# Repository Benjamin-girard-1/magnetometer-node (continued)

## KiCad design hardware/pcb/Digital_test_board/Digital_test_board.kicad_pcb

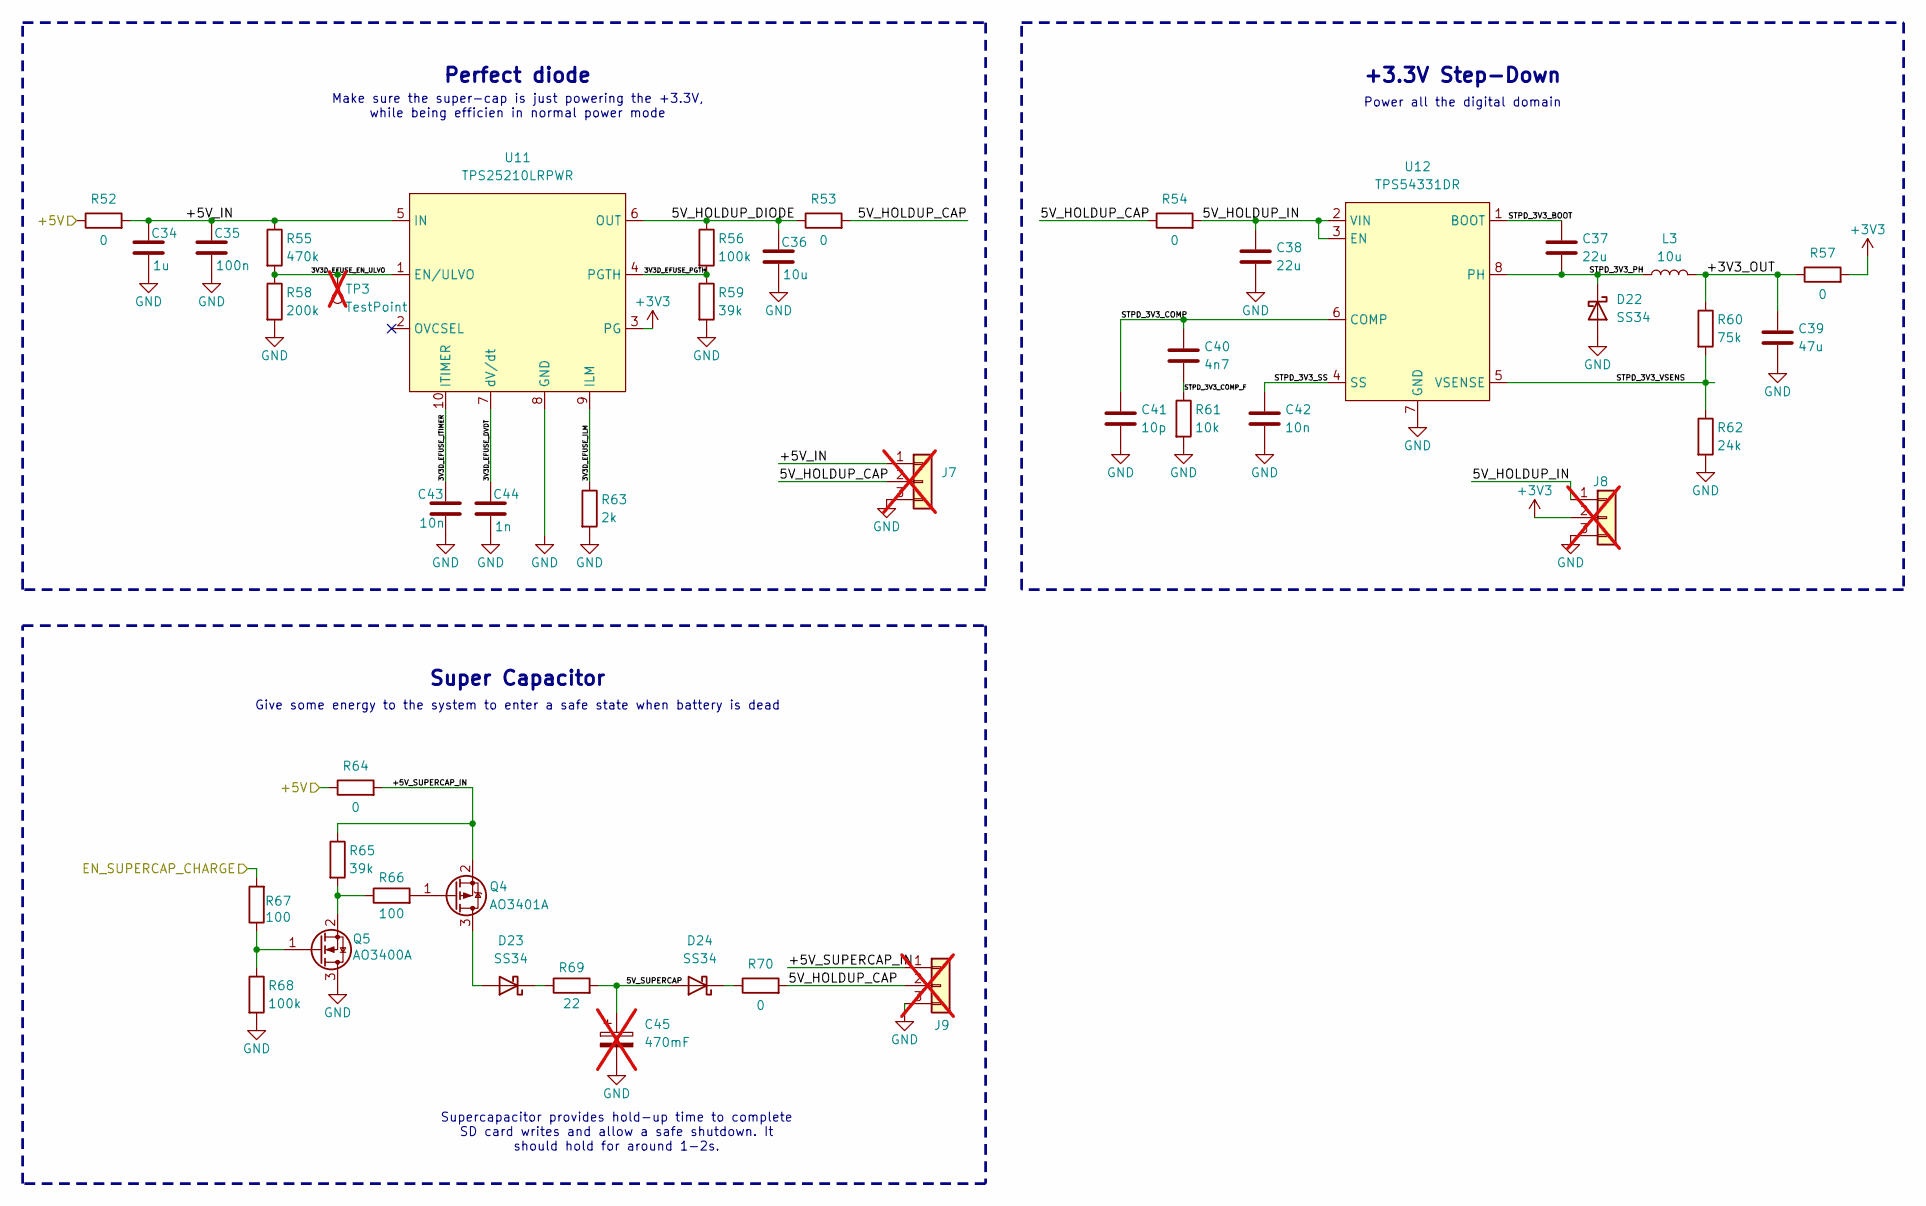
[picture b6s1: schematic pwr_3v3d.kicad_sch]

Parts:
C34: 1u; C_0805_2012Metric; LCSC C28323
C35: 100n; C_0603_1608Metric; LCSC C14663
C36: 10u; C_0805_2012Metric; LCSC C15850
C37, C38: 22u; C_1206_3216Metric; LCSC C12891
C39: 47u; C_1206_3216Metric; LCSC C96123
C40: 4n7; C_0603_1608Metric; LCSC C53987
C41: 10p; C_0603_1608Metric; LCSC C1634
C42, C43: 10n; C_0603_1608Metric; LCSC C57112
C44: 1n; C_0603_1608Metric; LCSC C1588
C45: 470mF; C_Radial_D8.0mm_P11.50mm; not fitted
D22, D23, D24: SS34; D_SMA; LCSC C8678
J7, J8, J9: Conn_01x03; PinHeader_1x03_P2.54mm_Vertical; not fitted
L3: 10u; L_Sunlord_MWSA0503S; LCSC C177248
Q4: AO3401A; SOT-23; LCSC C15127
Q5: AO3400A; SOT-23; LCSC C20917
R52, R53, R54, R57, R64, R70: 0; R_1206_3216Metric; LCSC C17888
R55: 470k; R_0603_1608Metric; LCSC C23178
R56, R68: 100k; R_0603_1608Metric; LCSC C25803
R58: 200k; R_0603_1608Metric; LCSC C25811
R59, R65: 39k; R_0603_1608Metric; LCSC C23153
R60: 75k; R_0603_1608Metric; LCSC C23242
R61: 10k; R_0603_1608Metric; LCSC C25804
R62: 24k; R_0603_1608Metric; LCSC C23352
R63: 2k; R_0603_1608Metric; LCSC C22975
R66, R67: 100; R_0603_1608Metric; LCSC C22775
R69: 22; R_2512_6332Metric; LCSC C2974113
TP3: TestPoint; TestPoint_THTPad_1.0x1.0mm_Drill0.5mm; not fitted
U11: TPS25210LRPWR; VQFN-HR-10; LCSC C2861226
U12: TPS54331DR; SOIC-8_3.9x4.9mm_P1.27mm; LCSC C9865

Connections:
+3V3: J8.2, R57.2, U11.3 (PG); also elsewhere on the board
+5V: R52.1, R64.1; also elsewhere on the board
/PWR_3V3D/3V3D_EFUSE_DVDT: C44.1, U11.7 (dV/dt)
/PWR_3V3D/3V3D_EFUSE_EN_ULVO: R55.2, R58.1, TP3.1, U11.1 (EN/ULVO)
/PWR_3V3D/3V3D_EFUSE_ILM: R63.1, U11.9 (ILM)
/PWR_3V3D/3V3D_EFUSE_ITIMER: C43.1, U11.10 (ITIMER)
/PWR_3V3D/3V3D_EFUSE_PGTH: R56.2, R59.1, U11.4 (PGTH)
/PWR_3V3D/5V_CAP_CHG: D23.1 (K), R69.1
/PWR_3V3D/5V_HOLDUP: C36.1, R53.1, R56.1, U11.6 (OUT)
/PWR_3V3D/5V_HOLDUP_IN: C38.1, J8.1, R54.2, U12.2 (VIN), U12.3 (EN)
/PWR_3V3D/5V_HOLDUP_bridge: J7.2, J9.2, R53.2, R54.1, R70.2
/PWR_3V3D/5V_SUPERCAP: C45.1, D24.2 (A), R69.2
/PWR_3V3D/5V_SUPERCAP_OUT: D24.1 (K), R70.1
/PWR_3V3D/+3V3_OUT: C39.1, L3.2, R57.1, R60.1
/PWR_3V3D/+5V_CAP_CHG_SW: D23.2 (A), Q4.3 (D)
/PWR_3V3D/+5V_IN: C34.1, C35.1, J7.1, R52.2, R55.1, U11.5 (IN)
/PWR_3V3D/+5V_SUPERCAP_IN: J9.1, Q4.2 (S), R64.2, R65.1
/PWR_3V3D/STPD_3V3_BOOT: C37.1, U12.1 (BOOT)
/PWR_3V3D/STPD_3V3_COMP: C40.1, C41.1, U12.6 (COMP)
/PWR_3V3D/STPD_3V3_COMP_F: C40.2, R61.1
/PWR_3V3D/STPD_3V3_PH: C37.2, D22.1 (K), L3.1, U12.8 (PH)
/PWR_3V3D/STPD_3V3_SS: C42.1, U12.4 (SS)
/PWR_3V3D/STPD_3V3_VSENS: R60.2, R62.1, U12.5 (VSENSE)
/PWR_3V3D/SUPERCAP_CHG_GATE: Q4.1 (G), R66.2
/PWR_3V3D/SUPERCAP_CHG_GATE_PULL: Q5.2 (S), R65.2, R66.1
GND: C34.2, C35.2, C36.2, C38.2, C39.2, C41.2, C42.2, C43.2, C44.2, C45.2, D22.2 (A), J7.3, J8.3, J9.3, Q5.3 (D), R58.2, R59.2, R61.2, R62.2, R63.2, R68.2, U11.8 (GND), U12.7 (GND); also elsewhere on the board

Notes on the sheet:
Make sure the super-cap is just powering the +3.3V, while being efficien in normal power mode
Super Capacitor
Give some energy to the system to enter a safe state when battery is dead
+3.3V Step-Down
Power all the digital domain
Supercapacitor provides hold-up time to complete SD card writes and allow a safe shutdown. It should hold for around 1-2s.
Perfect diode

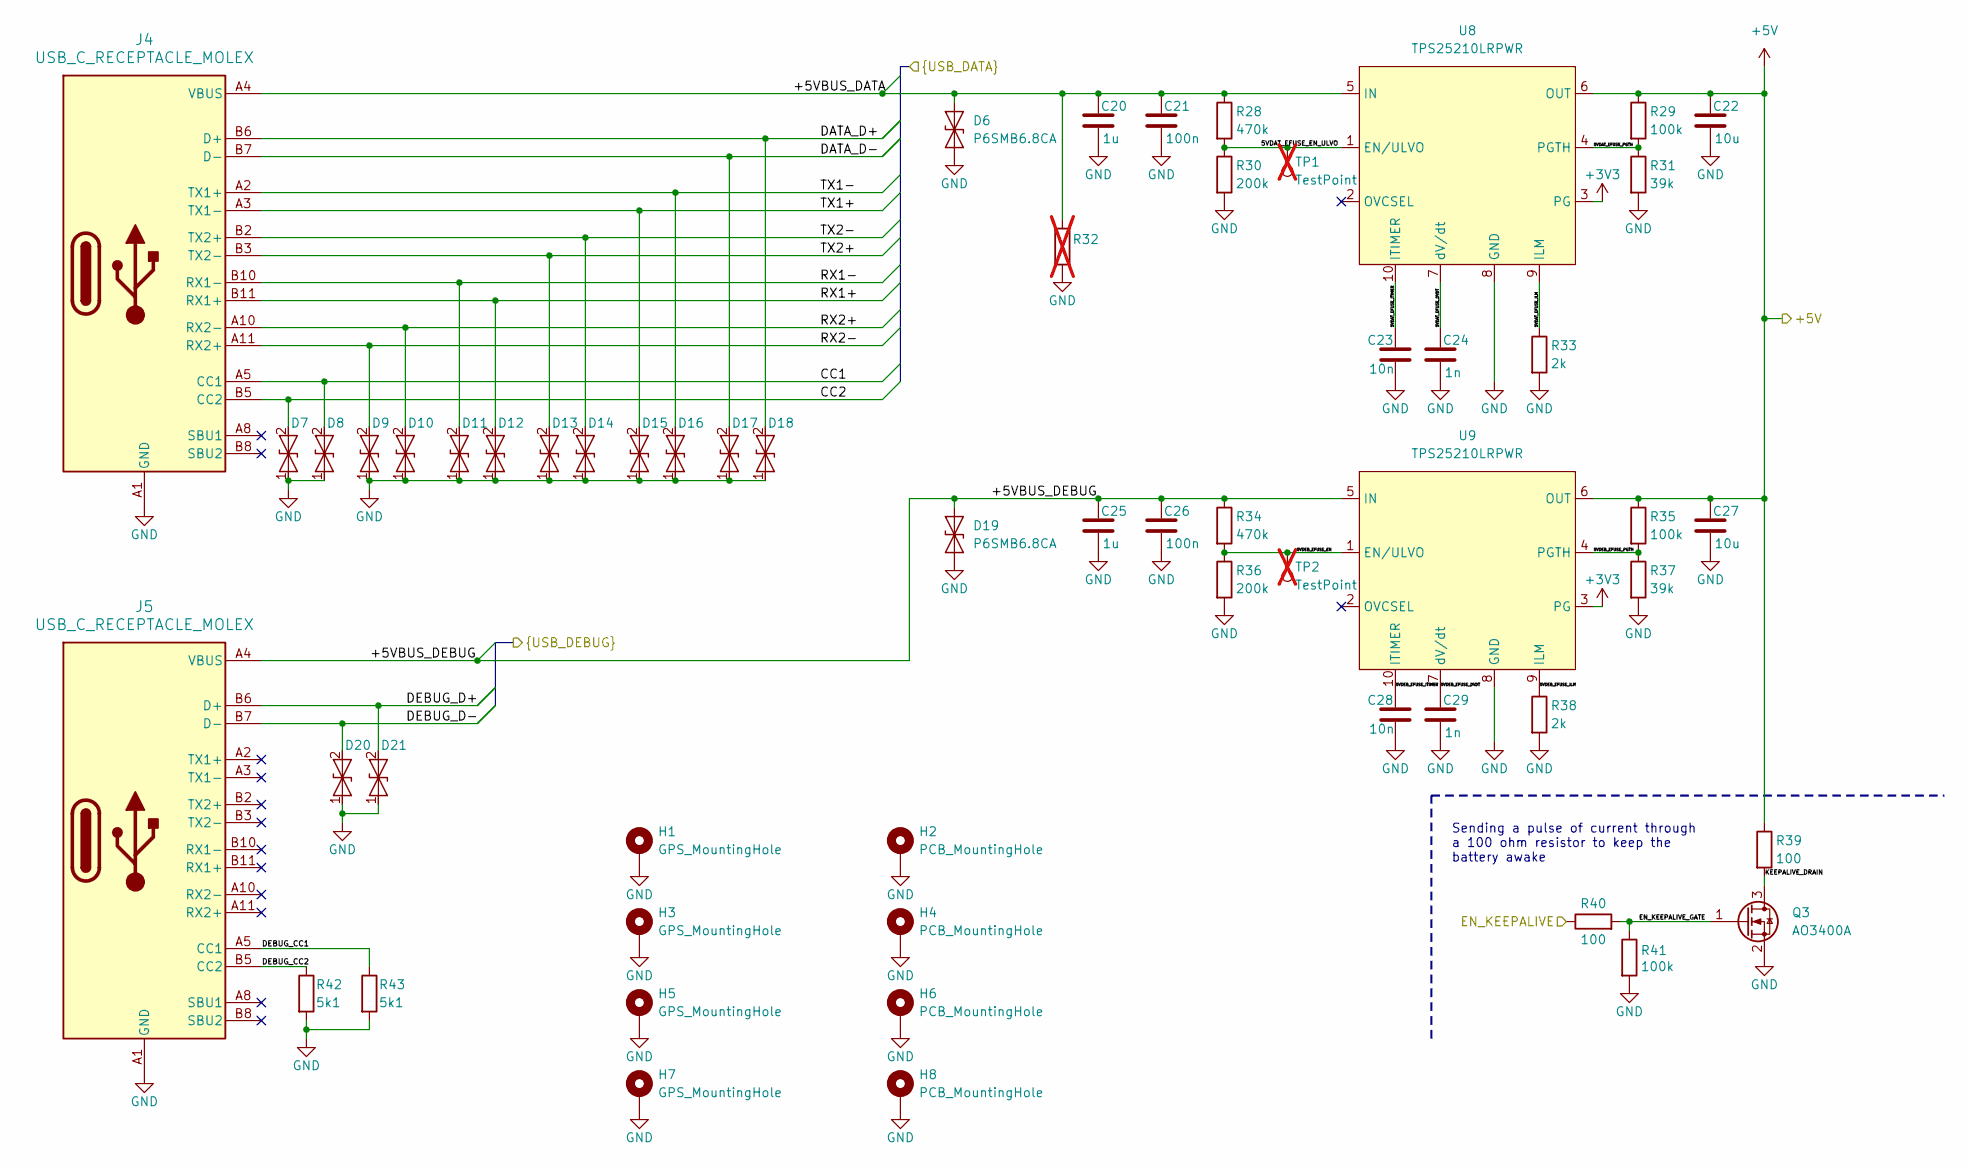
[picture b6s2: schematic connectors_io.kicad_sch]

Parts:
C20, C25: 1u; C_0805_2012Metric; LCSC C28323
C21, C26: 100n; C_0603_1608Metric; LCSC C14663
C22, C27: 10u; C_0805_2012Metric; LCSC C15850
C23, C28: 10n; C_0603_1608Metric; LCSC C57112
C24, C29: 1n; C_0603_1608Metric; LCSC C1588
D6, D19: P6SMB6.8CA; D_SMB; LCSC C7420377
D7, D8, D9, D10, D11, D12, D13, D14, D15, D16, D17, D18, D20, D21: H5VUD5BB; D_SOD-523; LCSC C20615820
H1, H3, H5, H7: GPS_MountingHole; MountingHole_3.2mm_M3_DIN965_Pad_TopBottom
H2, H4, H6, H8: PCB_MountingHole; MountingHole_3.2mm_M3_DIN965_Pad_TopBottom
J4, J5: USB_C_RECEPTACLE_MOLEX; CONN_201267-0005_MOL; LCSC C565324
Q3: AO3400A; SOT-23; LCSC C20917
R28, R34: 470k; R_0603_1608Metric; LCSC C23178
R29, R35, R41: 100k; R_0603_1608Metric; LCSC C25803
R30, R36: 200k; R_0603_1608Metric; LCSC C25811
R31, R37: 39k; R_0603_1608Metric; LCSC C23153
R32: R_1206_3216Metric_Pad1.30x1.75mm_HandSolder; not fitted
R33, R38: 2k; R_0603_1608Metric; LCSC C22975
R39, R40: 100; R_0603_1608Metric; LCSC C22775
R42, R43: 5k1; R_0603_1608Metric; LCSC C23186
TP1, TP2: TestPoint; TestPoint_THTPad_1.0x1.0mm_Drill0.5mm; not fitted
U8, U9: TPS25210LRPWR; VQFN-HR-10; LCSC C2861226

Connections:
+3V3: U8.3 (PG), U9.3 (PG); also elsewhere on the board
+5V: C22.1, C27.1, R29.1, R35.1, R39.1, U8.6 (OUT), U9.6 (OUT); also elsewhere on the board
/DATA_SAVING/+5VBUS_DATA: C20.1, C21.1, D6.2 (A2), J4.A4 (VBUS), J4.A9 (VBUS), J4.B4 (VBUS), J4.B9 (VBUS), R28.1, R32.2, U8.5 (IN); also elsewhere on the board
/DATA_SAVING/CC1: D8.2, J4.A5 (CC1); also elsewhere on the board
/DATA_SAVING/CC2: D7.2, J4.B5 (CC2); also elsewhere on the board
/DATA_SAVING/DATA_D+: D18.2, J4.A6 (D+), J4.B6 (D+); also elsewhere on the board
/DATA_SAVING/DATA_D-: D17.2, J4.A7 (D-), J4.B7 (D-); also elsewhere on the board
/DATA_SAVING/RX1+: D12.2, J4.B11 (RX1+); also elsewhere on the board
/DATA_SAVING/RX1-: D11.2, J4.B10 (RX1-); also elsewhere on the board
/DATA_SAVING/RX2+: D10.2, J4.A10 (RX2-); also elsewhere on the board
/DATA_SAVING/RX2-: D9.2, J4.A11 (RX2+); also elsewhere on the board
/DATA_SAVING/TX1+: D15.2, J4.A3 (TX1-); also elsewhere on the board
/DATA_SAVING/TX1-: D16.2, J4.A2 (TX1+); also elsewhere on the board
/DATA_SAVING/TX2+: D13.2, J4.B3 (TX2-); also elsewhere on the board
/DATA_SAVING/TX2-: D14.2, J4.B2 (TX2+); also elsewhere on the board
/IO_CONNECTOR/5VDAT_EFUSE_DVDT: C24.1, U8.7 (dV/dt)
/IO_CONNECTOR/5VDAT_EFUSE_EN_ULVO: R28.2, R30.1, TP1.1, U8.1 (EN/ULVO)
/IO_CONNECTOR/5VDAT_EFUSE_ILM: R33.1, U8.9 (ILM)
/IO_CONNECTOR/5VDAT_EFUSE_ITIMER: C23.1, U8.10 (ITIMER)
/IO_CONNECTOR/5VDAT_EFUSE_PGTH: R29.2, R31.1, U8.4 (PGTH)
/IO_CONNECTOR/5VDEB_EFUSE_DVDT: C29.1, U9.7 (dV/dt)
/IO_CONNECTOR/5VDEB_EFUSE_EN: R34.2, R36.1, TP2.1, U9.1 (EN/ULVO)
/IO_CONNECTOR/5VDEB_EFUSE_ILM: R38.1, U9.9 (ILM)
/IO_CONNECTOR/5VDEB_EFUSE_ITIMER: C28.1, U9.10 (ITIMER)
/IO_CONNECTOR/5VDEB_EFUSE_PGTH: R35.2, R37.1, U9.4 (PGTH)
/IO_CONNECTOR/+5VBUS_DEBUG: C25.1, C26.1, D19.2 (A2), J5.A4 (VBUS), J5.A9 (VBUS), J5.B4 (VBUS), J5.B9 (VBUS), R34.1, U9.5 (IN); also elsewhere on the board
/IO_CONNECTOR/DEBUG_CC1: J5.A5 (CC1), R43.1
/IO_CONNECTOR/DEBUG_CC2: J5.B5 (CC2), R42.1
/IO_CONNECTOR/DEBUG_D+: D21.2, J5.A6 (D+), J5.B6 (D+); also elsewhere on the board
/IO_CONNECTOR/DEBUG_D-: D20.2, J5.A7 (D-), J5.B7 (D-); also elsewhere on the board
/IO_CONNECTOR/EN_KEEPALIVE: R40.1; also elsewhere on the board
/IO_CONNECTOR/EN_KEEPALIVE_GATE: Q3.1 (G), R40.2, R41.1
/IO_CONNECTOR/KEEPALIVE_DRAIN: Q3.3 (D), R39.2
GND: C20.2, C21.2, C22.2, C23.2, C24.2, C25.2, C26.2, C27.2, C28.2, C29.2, D6.1 (A1), D7.1, D8.1, D9.1, D10.1, D11.1, D12.1, D13.1, D14.1, D15.1, D16.1, D17.1, D18.1, D19.1 (A1), D20.1, D21.1, H1.1, H2.1, H3.1, H4.1, H5.1, H6.1, H7.1, H8.1, J4.A1 (GND), J4.A12 (GND), J4.B1 (GND), J4.B12 (GND), J5.A1 (GND), J5.A12 (GND), J5.B1 (GND), J5.B12 (GND), Q3.2 (S), R30.2, R31.2, R32.1, R33.2, R36.2, R37.2, R38.2, R41.2, R42.2, R43.2, U8.8 (GND), U9.8 (GND); also elsewhere on the board

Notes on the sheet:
Sending a pulse of current through a 100 ohm resistor to keep the battery awake

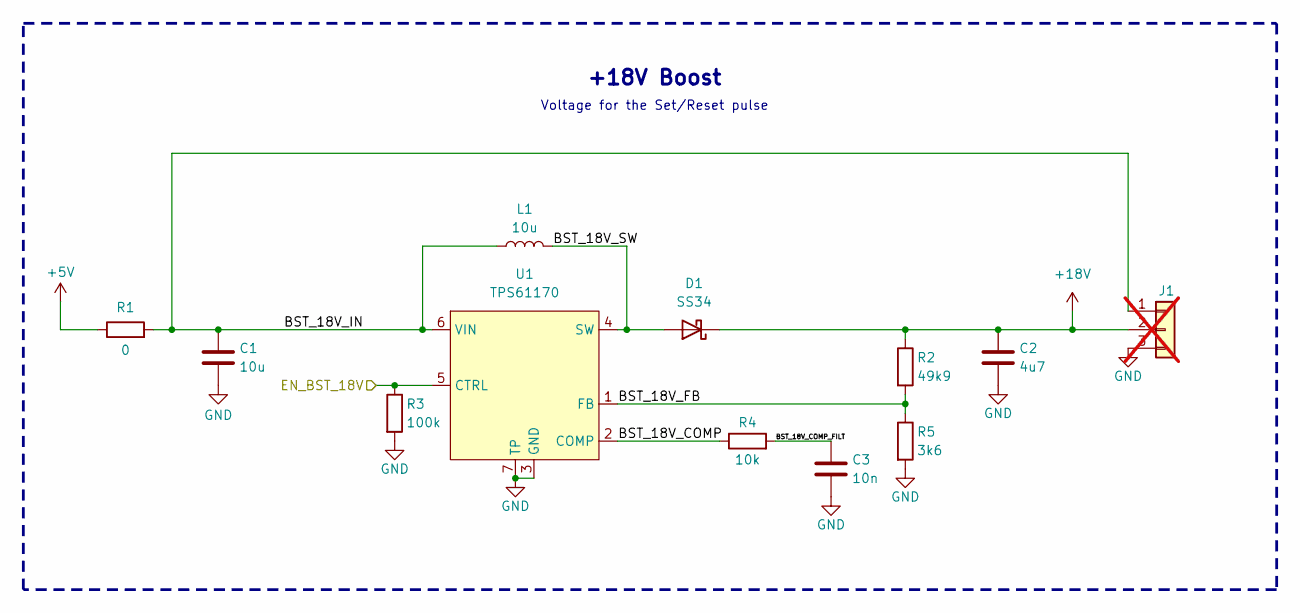
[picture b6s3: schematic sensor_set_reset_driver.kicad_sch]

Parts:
C1: 10u; C_0805_2012Metric; LCSC C15850
C2: 4u7; C_1206_3216Metric; LCSC C29823
C3: 10n; C_0603_1608Metric; LCSC C57112
D1: SS34; D_SMA; LCSC C8678
J1: Conn_01x03; PinHeader_1x03_P2.54mm_Vertical; not fitted
L1: 10u; L_Sunlord_MWSA0503S; LCSC C177248
R1: 0; R_1206_3216Metric; LCSC C17888
R2: 49k9; R_0603_1608Metric; LCSC C23184
R3: 100k; R_0603_1608Metric; LCSC C25803
R4: 10k; R_0603_1608Metric; LCSC C25804
R5: 3k6; R_0603_1608Metric; LCSC C22980
U1: TPS61170; WSON-6-1EP_2x2mm_P0.65mm_EP1x1.6mm; LCSC C15163

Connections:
+5V: R1.1; also elsewhere on the board
+18V: C2.1, D1.1 (K), J1.2, R2.1
/MCU_ESP32S3/EN_BST_18V: R3.1, U1.5 (CTRL); also elsewhere on the board
/SENSOR_SET_RESET_DRIVER/BST_18V_COMP: R4.1, U1.2 (COMP)
/SENSOR_SET_RESET_DRIVER/BST_18V_COMP_FILT: C3.1, R4.2
/SENSOR_SET_RESET_DRIVER/BST_18V_FB: R2.2, R5.1, U1.1 (FB)
/SENSOR_SET_RESET_DRIVER/BST_18V_IN: C1.1, J1.1, L1.1, R1.2, U1.6 (VIN)
/SENSOR_SET_RESET_DRIVER/BST_18V_SW: D1.2 (A), L1.2, U1.4 (SW)
GND: C1.2, C2.2, C3.2, J1.3, R3.2, R5.2, U1.3 (GND), U1.7 (TP); also elsewhere on the board

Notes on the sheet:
+18V Boost
Voltage for the Set/Reset pulse

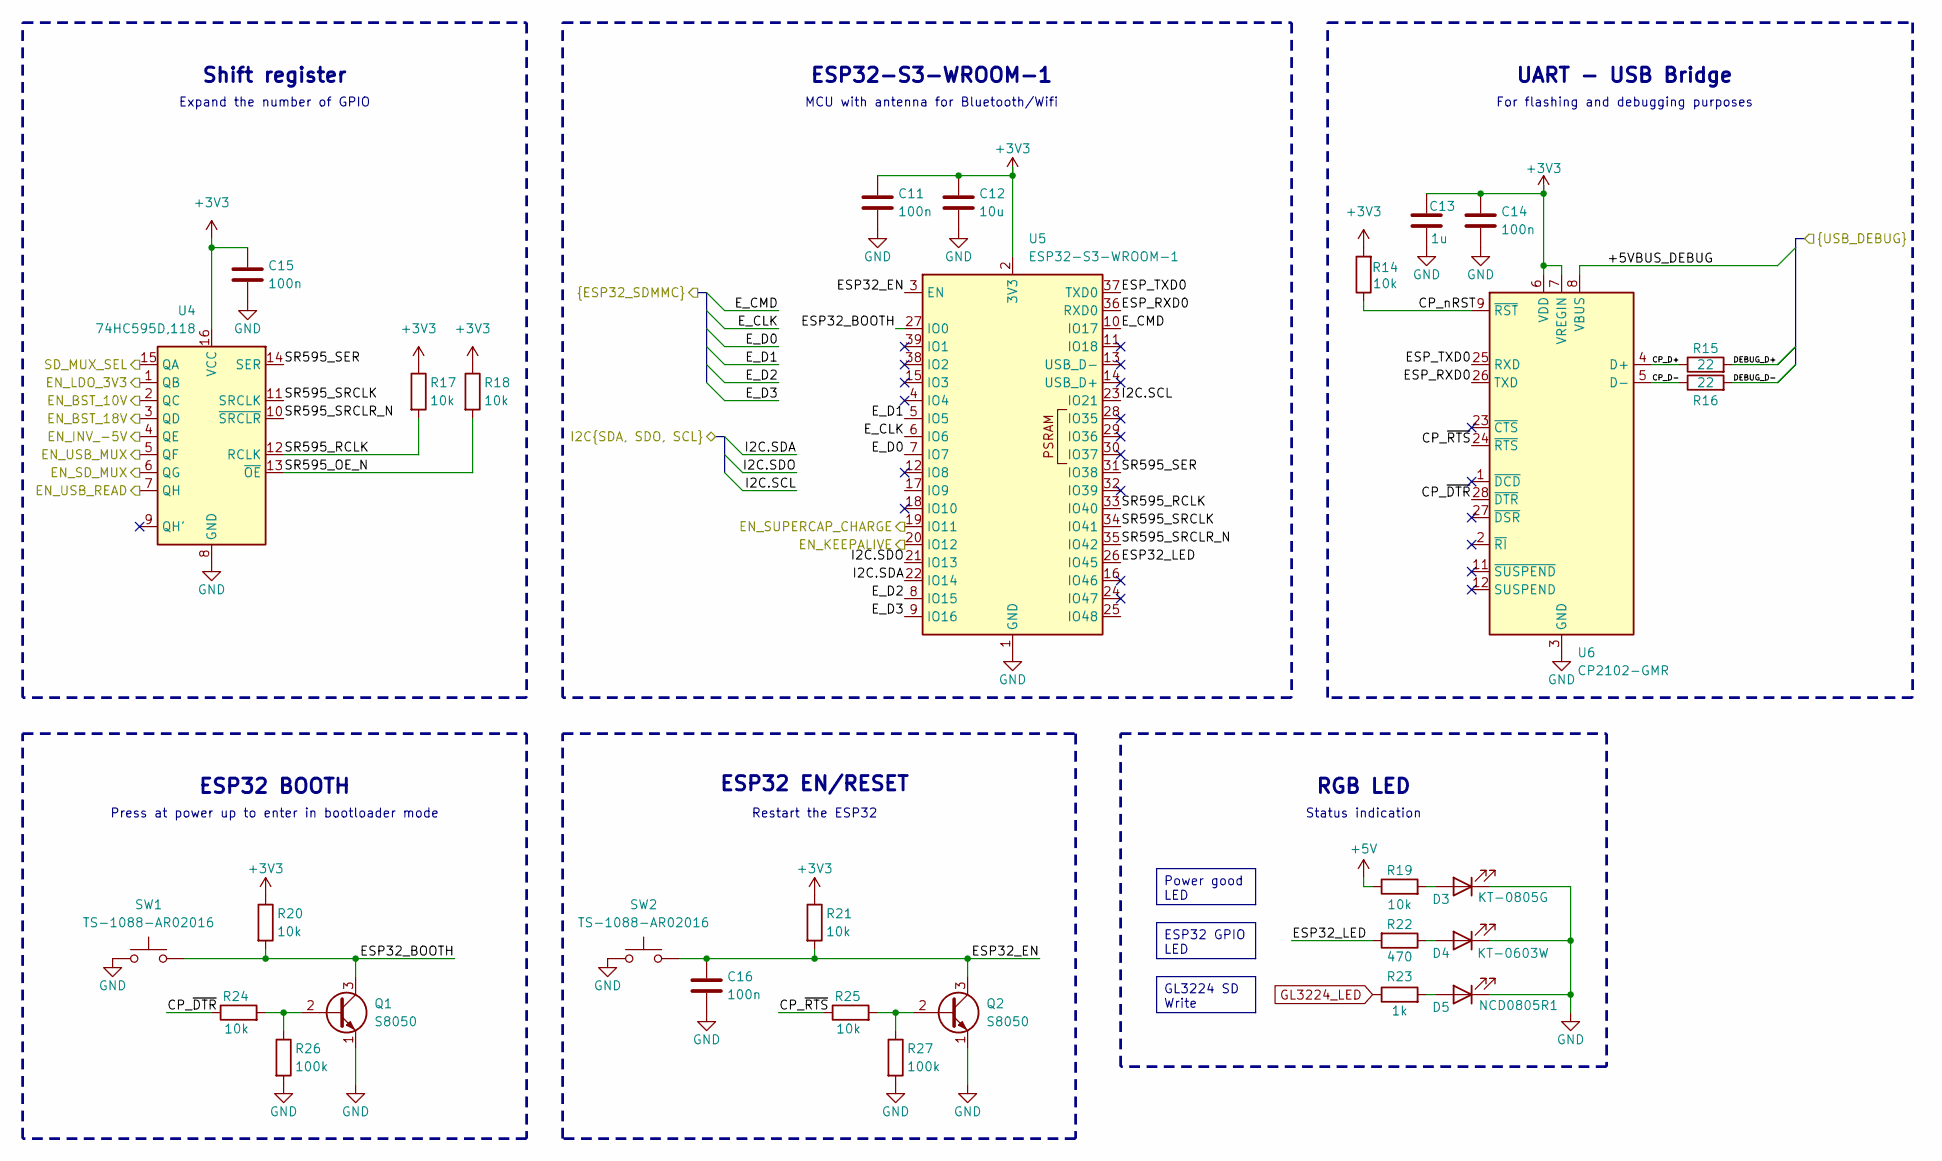
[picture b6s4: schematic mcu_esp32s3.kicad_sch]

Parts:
C11, C14, C15, C16: 100n; C_0603_1608Metric; LCSC C14663
C12: 10u; C_0805_2012Metric; LCSC C15850
C13: 1u; C_0805_2012Metric; LCSC C28323
D3: KT-0805G; LED_0805_2012Metric; LCSC C2297
D4: KT-0603W; LED_0603_1608Metric; LCSC C2290
D5: NCD0805R1; LED_0805_2012Metric; LCSC C84256
Q1, Q2: S8050; SOT-23; LCSC C2146
R14, R17, R18, R19, R20, R21, R24, R25: 10k; R_0603_1608Metric; LCSC C25804
R15, R16: 22; R_0603_1608Metric; LCSC C23345
R22: 470; R_0603_1608Metric; LCSC C23179
R23: 1k; R_0603_1608Metric; LCSC C21190
R26, R27: 100k; R_0603_1608Metric; LCSC C25803
SW1, SW2: TS-1088-AR02016; LCSC C720477
U4: 74HC595D,118; SOIC-16_3.9x9.9mm_P1.27mm; LCSC C5947
U5: ESP32-S3-WROOM-1; LCSC C2913202
U6: CP2102-GMR; QFN-28-1EP_5x5mm_P0.5mm_EP3.25x3.25mm; LCSC C6568

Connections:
+3V3: C11.1, C12.1, C13.1, C14.1, C15.1, R14.2, R17.1, R18.1, R20.1, R21.1, U4.16 (VCC), U5.2 (3V3), U6.6 (VDD), U6.7 (VREGIN); also elsewhere on the board
+5V: R19.1; also elsewhere on the board
/DATA_SAVING/EN_SD_MUX: U4.6 (QG); also elsewhere on the board
/DATA_SAVING/EN_USB_MUX: U4.5 (QF); also elsewhere on the board
/DATA_SAVING/EN_USB_READ: U4.7 (QH); also elsewhere on the board
/DATA_SAVING/E_CLK: U5.6 (IO6); also elsewhere on the board
/DATA_SAVING/E_CMD: U5.10 (IO17); also elsewhere on the board
/DATA_SAVING/E_D0: U5.7 (IO7); also elsewhere on the board
/DATA_SAVING/E_D1: U5.5 (IO5); also elsewhere on the board
/DATA_SAVING/E_D2: U5.8 (IO15); also elsewhere on the board
/DATA_SAVING/E_D3: U5.9 (IO16); also elsewhere on the board
/DATA_SAVING/SD_MUX_SEL: U4.15 (QA); also elsewhere on the board
/IMU/I2C.SCL: U5.23 (IO21); also elsewhere on the board
/IMU/I2C.SDA: U5.22 (IO14); also elsewhere on the board
/IMU/I2C.SDO: U5.21 (IO13); also elsewhere on the board
/IO_CONNECTOR/+5VBUS_DEBUG: U6.8 (VBUS); also elsewhere on the board
/IO_CONNECTOR/DEBUG_D+: R15.2; also elsewhere on the board
/IO_CONNECTOR/DEBUG_D-: R16.2; also elsewhere on the board
/IO_CONNECTOR/EN_KEEPALIVE: U5.20 (IO12); also elsewhere on the board
/MCU_ESP32S3/CP_D+: R15.1, U6.4 (D+)
/MCU_ESP32S3/CP_D-: R16.1, U6.5 (D-)
/MCU_ESP32S3/CP_nRST: R14.1, U6.9 (~RST)
/MCU_ESP32S3/CP_~DTR: R24.1, U6.28 (~DTR)
/MCU_ESP32S3/CP_~RTS: R25.1, U6.24 (~RTS)
/MCU_ESP32S3/EN_BST_10V: U4.2 (QC); also elsewhere on the board
/MCU_ESP32S3/EN_BST_18V: U4.3 (QD); also elsewhere on the board
/MCU_ESP32S3/EN_INV_-5V: U4.4 (QE); also elsewhere on the board
/MCU_ESP32S3/EN_LDO_3V3: U4.1 (QB); also elsewhere on the board
/MCU_ESP32S3/ESP32_BOOTH: Q1.3 (C), R20.2, SW1.2, U5.27 (IO0)
/MCU_ESP32S3/ESP32_EN: C16.1, Q2.3 (C), R21.2, SW2.2, U5.3 (EN)
/MCU_ESP32S3/ESP32_LED: R22.2, U5.26 (IO45)
/MCU_ESP32S3/ESP_RXD0: U5.36 (RXD0), U6.26 (TXD)
/MCU_ESP32S3/ESP_TXD0: U5.37 (TXD0), U6.25 (RXD)
/MCU_ESP32S3/SR595_OE_N: R18.2, U4.13 (~OE)
/MCU_ESP32S3/SR595_RCLK: R17.2, U4.12 (RCLK), U5.33 (IO40)
/MCU_ESP32S3/SR595_SER: U4.14 (SER), U5.31 (IO38)
/MCU_ESP32S3/SR595_SRCLK: U4.11 (SRCLK), U5.34 (IO41)
/MCU_ESP32S3/SR595_SRCLR_N: U4.10 (~SRCLR), U5.35 (IO42)
GL3224_LED: R23.1; also elsewhere on the board
GND: C11.2, C12.2, C13.2, C14.2, C15.2, C16.2, D3.1 (K), D4.1 (K), D5.1 (K), Q1.1 (E), Q2.1 (E), R26.2, R27.2, SW1.1, SW2.1, U4.8 (GND), U5.1 (GND), U5.40 (GND), U5.41 (GND), U6.3 (GND), U6.29 (GND); also elsewhere on the board
unnamed: D3.2 (A), R19.2
unnamed: D4.2 (A), R22.1
unnamed: D5.2 (A), R23.2
unnamed: Q1.2 (B), R24.2, R26.1
unnamed: Q2.2 (B), R25.2, R27.1

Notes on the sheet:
Shift register
Expand the number of GPIO
Restart the ESP32
ESP32-S3-WROOM-1
Press at power up to enter in bootloader mode
ESP32 BOOTH
Status indication
MCU with antenna for Bluetooth/Wifi
ESP32 EN/RESET
For flashing and debugging purposes
UART - USB Bridge
RGB LED
ESP32 GPIO LED
Power good LED
GL3224 SD Write

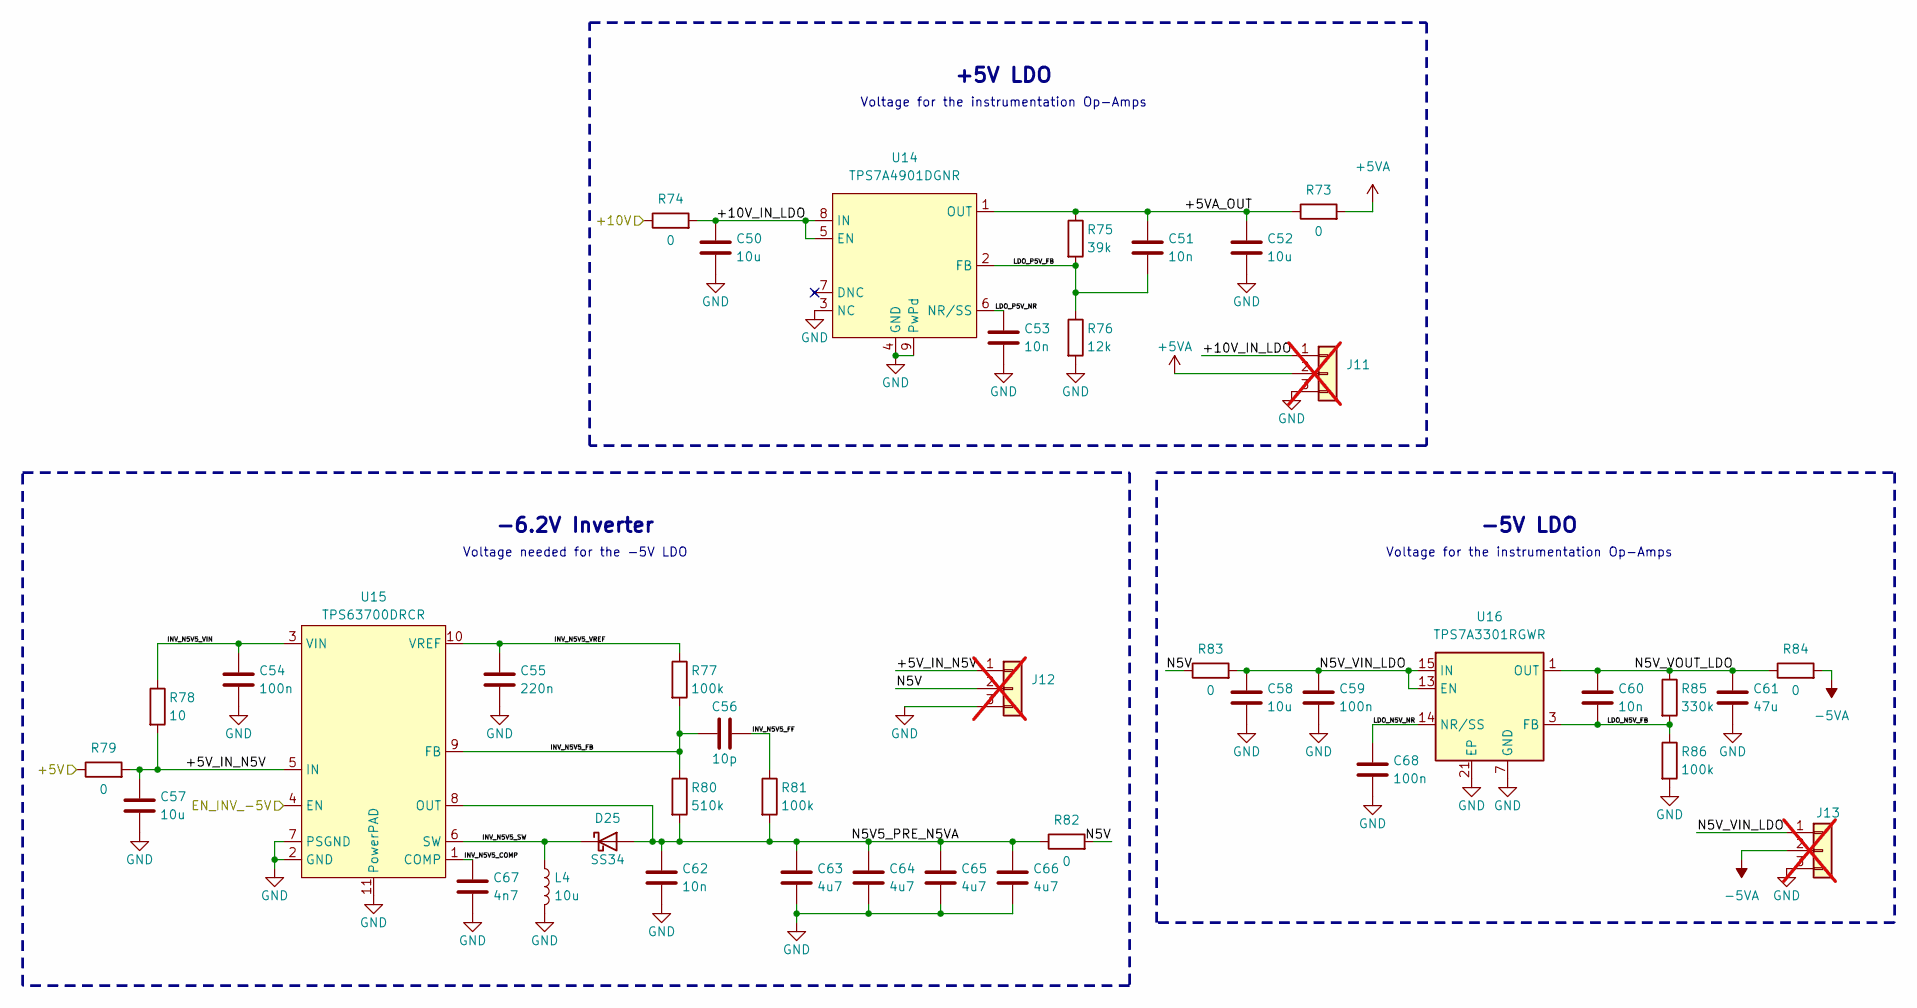
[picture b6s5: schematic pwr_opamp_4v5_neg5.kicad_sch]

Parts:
C50, C52, C57, C58: 10u; C_0805_2012Metric; LCSC C15850
C51, C53, C60, C62: 10n; C_0603_1608Metric; LCSC C57112
C54, C59, C68: 100n; C_0603_1608Metric; LCSC C14663
C55: 220n; C_0603_1608Metric; LCSC C21120
C56: 10p; C_0603_1608Metric; LCSC C1634
C61: 47u; C_1206_3216Metric; LCSC C96123
C63, C64, C65, C66: 4u7; C_1206_3216Metric; LCSC C29823
C67: 4n7; C_0603_1608Metric; LCSC C53987
D25: SS34; D_SMA; LCSC C8678
J11, J12, J13: Conn_01x03; PinHeader_1x03_P2.54mm_Vertical; not fitted
L4: 10u; L_Sunlord_MWSA0503S; LCSC C177248
R73, R74, R79, R82, R83, R84: 0; R_1206_3216Metric; LCSC C17888
R75: 39k; R_0603_1608Metric; LCSC C23153
R76: 12k; R_0603_1608Metric; LCSC C22790
R77, R81, R86: 100k; R_0603_1608Metric; LCSC C25803
R78: 10; R_0603_1608Metric; LCSC C22859
R80: 510k; R_0603_1608Metric; LCSC C23192
R85: 330k; R_0603_1608Metric; LCSC C23137
U14: TPS7A4901DGNR; HVSSOP-8-1EP_3x3mm_P0.65mm_EP1.57x1.89mm; LCSC C16430
U15: TPS63700DRCR; VSON-10-1EP_3x3mm_P0.5mm_EP1.2x2mm; LCSC C54792
U16: TPS7A3301RGWR; Texas_RGW0020A_VQFN-20-1EP_5x5mm_P0.65mm_EP3.15x3.15mm; LCSC C90082

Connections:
+5V: R79.1; also elsewhere on the board
+5VA: J11.2, R73.2
-5VA: J13.2, R84.2
/MCU_ESP32S3/EN_INV_-5V: U15.4 (EN); also elsewhere on the board
/PWR_5VA_NEG5/+5VA_OUT: C51.1, C52.1, R73.1, R75.1, U14.1 (OUT)
/PWR_5VA_NEG5/+5V_IN_N5V: C57.1, J12.1, R78.2, R79.2, U15.5 (IN)
/PWR_5VA_NEG5/+10V_IN_LDO: C50.1, J11.1, R74.2, U14.5 (EN), U14.8 (IN)
/PWR_5VA_NEG5/INV_N5V5_COMP: C67.1, U15.1 (COMP)
/PWR_5VA_NEG5/INV_N5V5_FB: C56.1, R77.2, R80.1, U15.9 (FB)
/PWR_5VA_NEG5/INV_N5V5_FF: C56.2, R81.1
/PWR_5VA_NEG5/INV_N5V5_SW: D25.1 (K), L4.1, U15.6 (SW)
/PWR_5VA_NEG5/INV_N5V5_VIN: C54.1, R78.1, U15.3 (VIN)
/PWR_5VA_NEG5/INV_N5V5_VREF: C55.1, R77.1, U15.10 (VREF)
/PWR_5VA_NEG5/LDO_N5V_FB: C60.2, R85.2, R86.1, U16.3 (FB)
/PWR_5VA_NEG5/LDO_N5V_NR: C68.1, U16.14 (NR/SS)
/PWR_5VA_NEG5/LDO_P5V_FB: C51.2, R75.2, R76.1, U14.2 (FB)
/PWR_5VA_NEG5/LDO_P5V_NR: C53.1, U14.6 (NR/SS)
/PWR_5VA_NEG5/N5V5_PRE_N5VA: C62.1, C63.1, C64.1, C65.1, C66.1, D25.2 (A), R80.2, R81.2, R82.1, U15.8 (OUT)
/PWR_5VA_NEG5/N5V5_PRE_N5VA_bridge: J12.2, R82.2, R83.1
/PWR_5VA_NEG5/N5V_VIN_LDO: C58.1, C59.1, J13.1, R83.2, U16.13 (EN), U16.15 (IN), U16.16 (IN)
/PWR_5VA_NEG5/N5V_VOUT_LDO: C60.1, C61.1, R84.1, R85.1, U16.1 (OUT), U16.20 (OUT)
/PWR_9V_BRIDGE/+10V: R74.1; also elsewhere on the board
GND: C50.2, C52.2, C53.2, C54.2, C55.2, C57.2, C58.2, C59.2, C61.2, C62.2, C63.2, C64.2, C65.2, C66.2, C67.2, C68.2, J11.3, J12.3, J13.3, L4.2, R76.2, R86.2, U14.3 (NC), U14.4 (GND), U14.9 (PwPd), U15.2 (GND), U15.7 (PSGND), U15.11 (PowerPAD), U16.7 (GND), U16.21 (EP); also elsewhere on the board

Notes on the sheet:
-5V LDO
Voltage for the instrumentation Op-Amps
Voltage needed for the -5V LDO
+5V LDO
-6.2V Inverter
